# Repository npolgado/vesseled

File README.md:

# vesseled
addressable led code and hardware source. using addressable LEDS and creating a custom board to control and productize

Hardware:
- [x] Base prototyped idea
- [ ] Create a custom board to control addressable LEDS

Software:
- [x] Basic LED control
- [ ] track mouse poisition
- [ ] more input based lighting

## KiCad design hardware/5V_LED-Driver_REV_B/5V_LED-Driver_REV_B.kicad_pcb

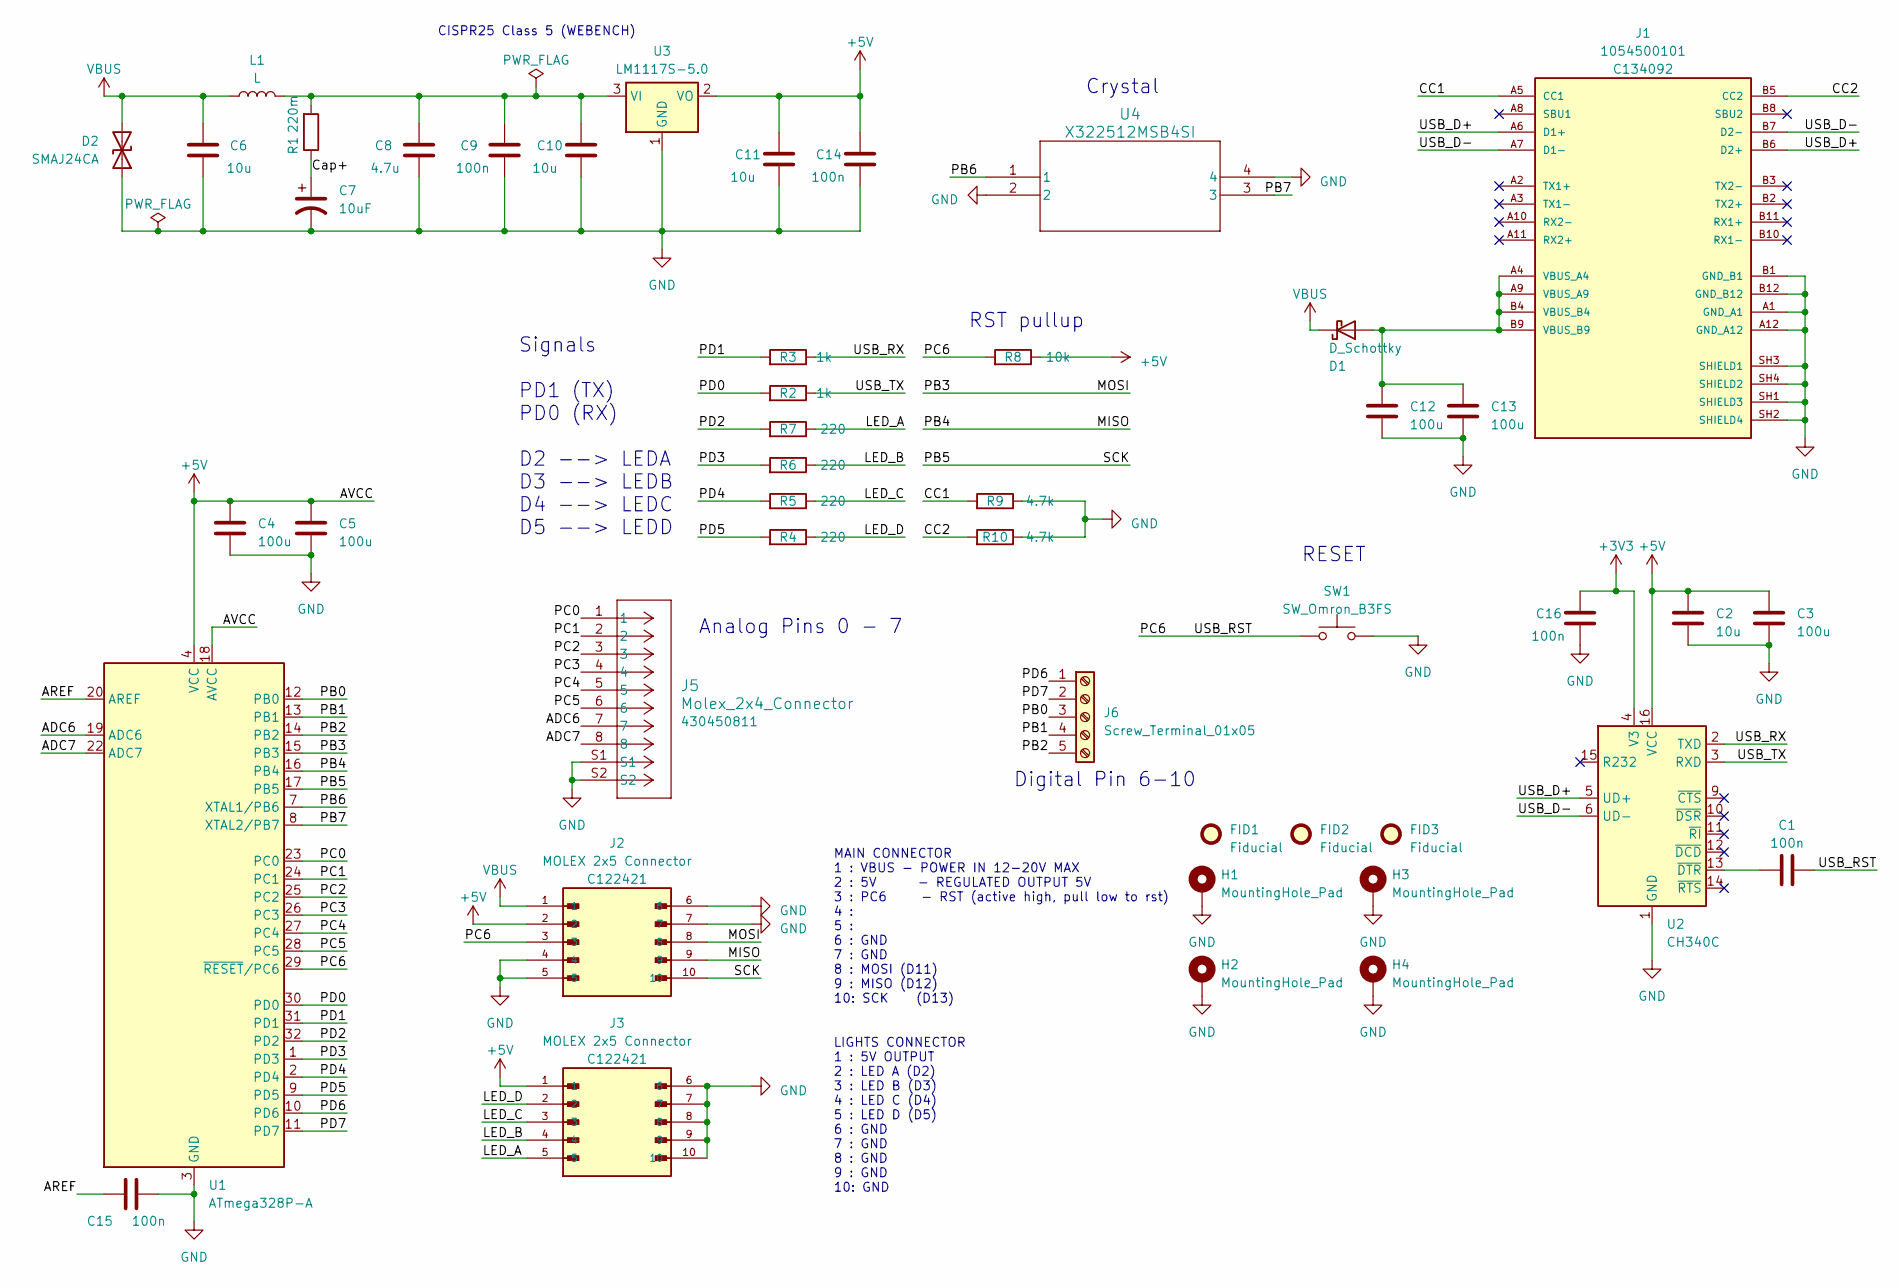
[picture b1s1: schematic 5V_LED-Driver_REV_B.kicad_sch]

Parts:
C1: 100n; C_0603_1608Metric
C2: 10u; C_0603_1608Metric
C3, C4, C5, C12, C13: 100u; C_0603_1608Metric
C6: 10u; L_1210_3225Metric; Manufacturer Part Number GRM32ER71H106KA12L; JLCPCB Part # C77102
C7: 10uF; CP_Elec_6.3x5.9; Manufacturer Part Number 50SVPF10M; JLCPCB Part # C2162323
C8: 4.7u; C_1206_3216Metric; Manufacturer Part Number GRM31CR71H475KA12L; JLCPCB Part # C77096
C9, C14, C15, C16: 100n; C_0603_1608Metric; Manufacturer Part Number GRM188R71H104KA93D; JLCPCB Part # C77055
C10, C11: 10u; C_0603_1608Metric; Manufacturer Part Number GRM188R71H104KA93D; JLCPCB Part # C77055
D1: D_Schottky; D_SMA
D2: SMAJ24CA; D_SMA; Manufacturer Part Number SMAJ24CA; JLCPCB Part # C148223
FID1, FID2, FID3: Fiducial; Fiducial_1mm_Mask2mm
H1, H2, H3, H4: MountingHole_Pad; MountingHole_3.2mm_M3_DIN965_Pad
J1: 1054500101; MOLEX_1054500101; PARTREV A7; JLCPCB Part # C134092
J2, J3: MOLEX 2x5 Connector; MOLEX_430451000; PARTREV G; JLCPCB Part # C122421
J5: Molex_2x4_Connector; MFG PN 430450811
J6: Screw_Terminal_01x05; TerminalBlock_bornier-5_P5.08mm
L1: L; L_0805_2012Metric; Manufacturer Part Number IHLP1212BZERR22M11; JLCPCB Part # C499512
R1: 220m; R_0603_1608Metric; Manufacturer Part Number RL0603FR-070R22L; JLCPCB Part # C326952
R2, R3: 1k; R_0603_1608Metric
R4, R5, R6, R7: 220; R_0603_1608Metric
R8: 10k; R_0603_1608Metric
R9, R10: 4.7k; R_0603_1608Metric
SW1: SW_Omron_B3FS; SW_SPST_Omron_B3FS-100xP
U1: ATmega328P-A; TQFP-32_7x7mm_P0.8mm
U2: CH340C; SOIC-16_3.9x9.9mm_P1.27mm
U3: LM1117S-5.0; TO-263-3_TabPin2
U4: X322512MSB4SI; SMD_2MSB4SI_YXC

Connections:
+3V3: C16.1, U2.4 (V3)
+5V: C2.1, C3.1, C4.1, C5.1, C11.1, C14.1, J2.2, J3.1, R8.1, U1.4 (VCC), U1.6 (VCC), U1.18 (AVCC), U2.16 (VCC), U3.2 (VO)
/ADC6: J5.7, U1.19 (ADC6)
/ADC7: J5.8, U1.22 (ADC7)
/AREF: C15.1, U1.20 (AREF)
/CC1: J1.A5 (CC1), R9.2
/CC2: J1.B5 (CC2), R10.2
/Cap+: C7.1, R1.1
/LED_A: J3.5, R7.1
/LED_B: J3.4, R6.1
/LED_C: J3.3, R5.1
/LED_D: J3.2, R4.1
/MISO: J2.9, U1.16 (PB4)
/MOSI: J2.8, U1.15 (PB3)
/PB0: J6.3, U1.12 (PB0)
/PB1: J6.4, U1.13 (PB1)
/PB2: J6.5, U1.14 (PB2)
/PB5: J2.10, U1.17 (PB5)
/PB6: U1.7 (XTAL1/PB6), U4.1
/PB7: U1.8 (XTAL2/PB7), U4.3
/PC0: J5.1, U1.23 (PC0)
/PC1: J5.2, U1.24 (PC1)
/PC2: J5.3, U1.25 (PC2)
/PC3: J5.4, U1.26 (PC3)
/PC4: J5.5, U1.27 (PC4)
/PC5: J5.6, U1.28 (PC5)
/PC6: C1.1, J2.3, R8.2, SW1.1, U1.29 (~RESET/PC6)
/PD0: R2.2, U1.30 (PD0)
/PD1: R3.2, U1.31 (PD1)
/PD2: R7.2, U1.32 (PD2)
/PD3: R6.2, U1.1 (PD3)
/PD4: R5.2, U1.2 (PD4)
/PD5: R4.2, U1.9 (PD5)
/PD6: J6.1, U1.10 (PD6)
/PD7: J6.2, U1.11 (PD7)
/USB_D+: J1.A6 (D1+), J1.B6 (D2+), U2.5 (UD+)
/USB_D-: J1.A7 (D1-), J1.B7 (D2-), U2.6 (UD-)
/USB_RX: R3.1, U2.2 (TXD)
/USB_TX: R2.1, U2.3 (RXD)
GND: C2.2, C3.2, C4.2, C5.2, C6.2, C7.2, C8.2, C9.2, C10.2, C11.2, C12.2, C13.2, C14.2, C15.2, C16.2, D2.1 (A1), H1.1, H2.1, H3.1, H4.1, J1.A1 (GND_A1), J1.A12 (GND_A12), J1.B1 (GND_B1), J1.B12 (GND_B12), J1.SH1 (SHIELD3), J1.SH2 (SHIELD4), J1.SH3 (SHIELD1), J1.SH4 (SHIELD2), J2.4, J2.5, J2.6, J2.7, J3.6, J3.7, J3.8, J3.9, J3.10, J5.S1, J5.S2, R9.1, R10.1, SW1.2, U1.3 (GND), U1.5 (GND), U1.21 (GND), U2.1 (GND), U3.1 (GND), U4.2, U4.4
unnamed: C8.1, C9.1, C10.1, L1.2, R1.2, U3.3 (VI)
unnamed: C12.1, C13.1, D1.2 (A), J1.A4 (VBUS_A4), J1.A9 (VBUS_A9), J1.B4 (VBUS_B4), J1.B9 (VBUS_B9)
unnamed: C1.2, U2.13 (~DTR)
VBUS: C6.1, D1.1 (K), D2.2 (A2), J2.1, L1.1

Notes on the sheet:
Crystal
RST pullup
CISPR25 Class 5 (WEBENCH)
Digital Pin 6-10
MAIN CONNECTOR 1 : VBUS - POWER IN 12-20V MAX 2 : 5V - REGULATED OUTPUT 5V 3 : PC6 - RST (active high, pull low to rst) 4 : 5 : 6 : GND 7 : GND 8 : MOSI (D11) 9 : MISO (D12) 10: SCK (D13)
Analog Pins 0 - 7
RESET
Signals PD1 (TX) PD0 (RX) D2 --> LEDA D3 --> LEDB D4 --> LEDC D5 --> LEDD
LIGHTS CONNECTOR 1 : 5V OUTPUT 2 : LED A (D2) 3 : LED B (D3) 4 : LED C (D4) 5 : LED D (D5) 6 : GND 7 : GND 8 : GND 9 : GND 10: GND

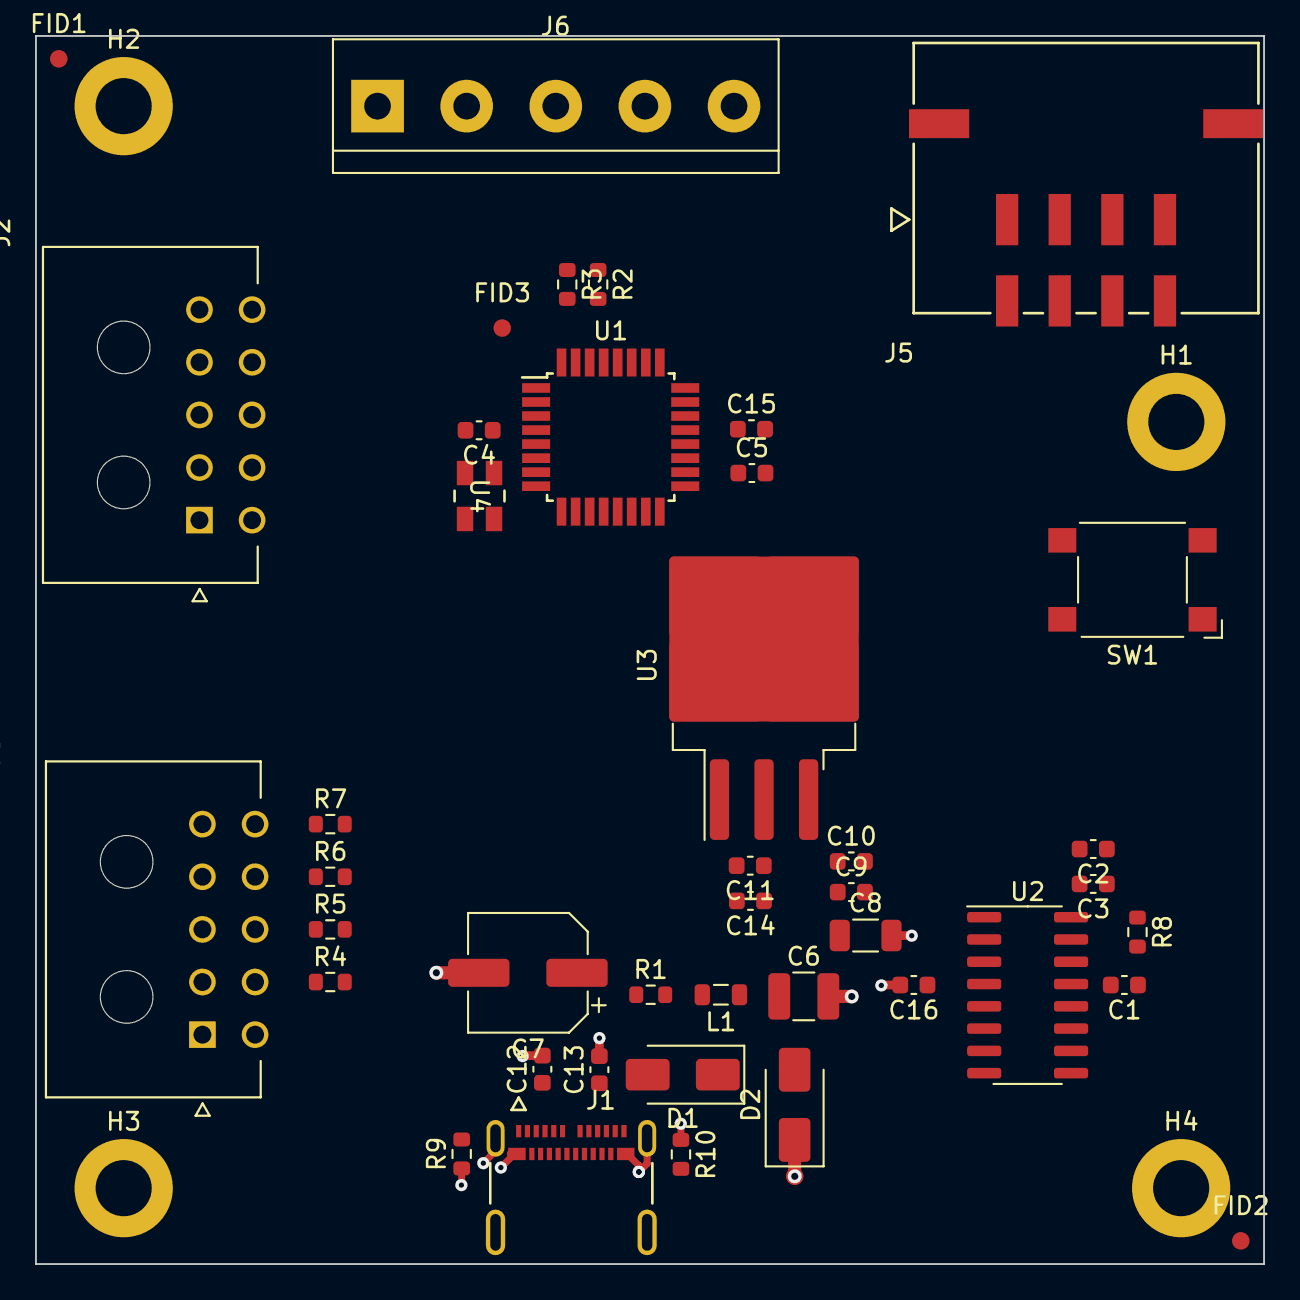
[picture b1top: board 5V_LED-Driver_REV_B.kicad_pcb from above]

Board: 4 copper layers, 70.0 x 70.0 mm, 46 parts (0 on the bottom side), 44 nets.

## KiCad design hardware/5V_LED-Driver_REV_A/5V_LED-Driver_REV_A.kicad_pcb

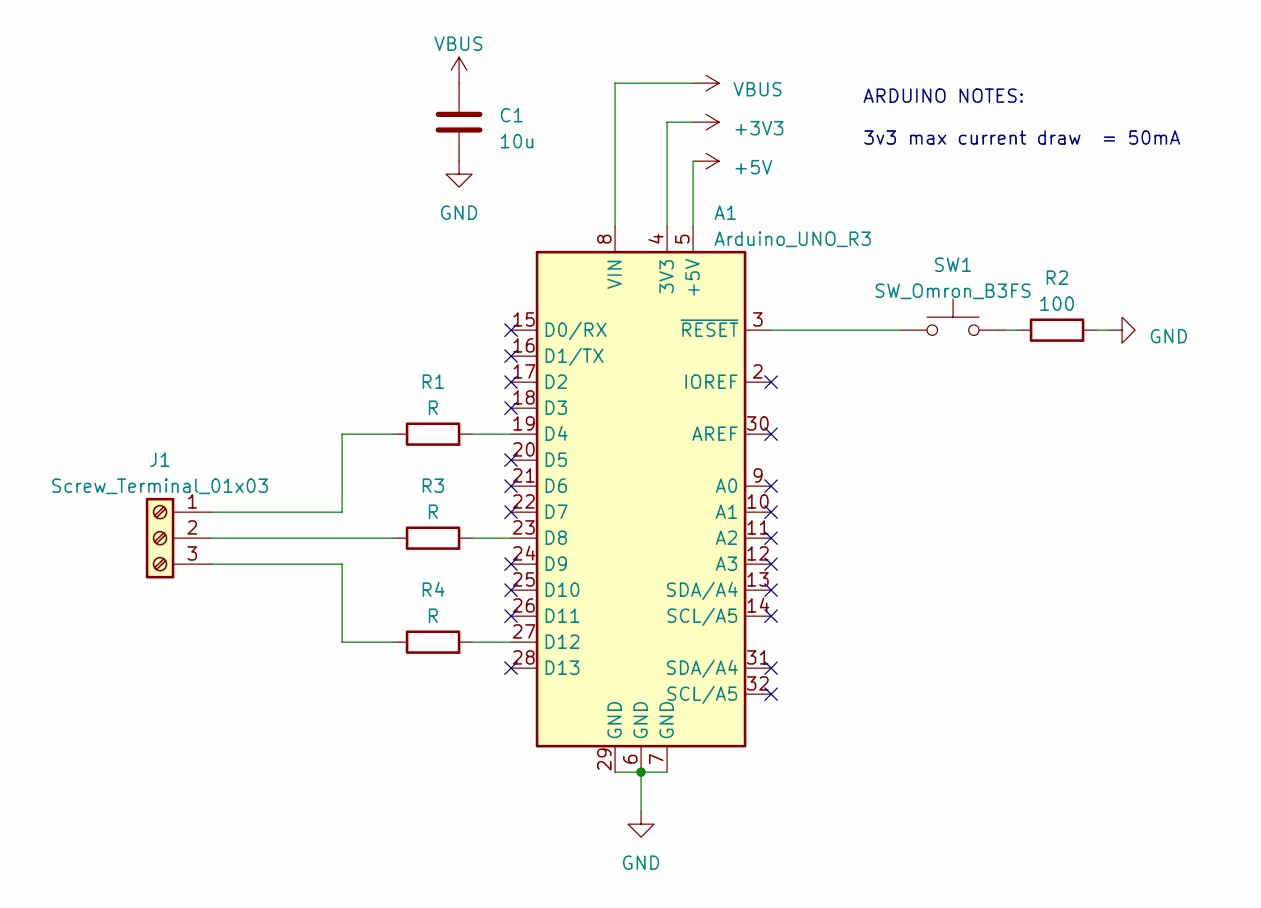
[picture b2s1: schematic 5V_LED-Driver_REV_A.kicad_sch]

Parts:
A1: Arduino_UNO_R3
C1: 10u; C_0603_1608Metric
J1: Screw_Terminal_01x03; TerminalBlock_Phoenix_MKDS-3-3-5.08_1x03_P5.08mm_Horizontal
R1, R3, R4: R; R_0603_1608Metric
R2: 100; R_0603_1608Metric
SW1: SW_Omron_B3FS; SW_SPST_Omron_B3FS-100xP

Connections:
+3V3: A1.4 (3V3)
+5V: A1.5 (+5V)
GND: A1.6 (GND), A1.7 (GND), A1.29 (GND), C1.2, R2.2
unnamed: A1.19 (D4), R1.2
unnamed: A1.23 (D8), R3.2
unnamed: A1.27 (D12), R4.2
unnamed: A1.3 (~RESET), SW1.1
unnamed: J1.1, R1.1
unnamed: J1.2, R3.1
unnamed: J1.3, R4.1
unnamed: R2.1, SW1.2
VBUS: A1.8 (VIN), C1.1

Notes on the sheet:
ARDUINO NOTES: 3v3 max current draw = 50mA

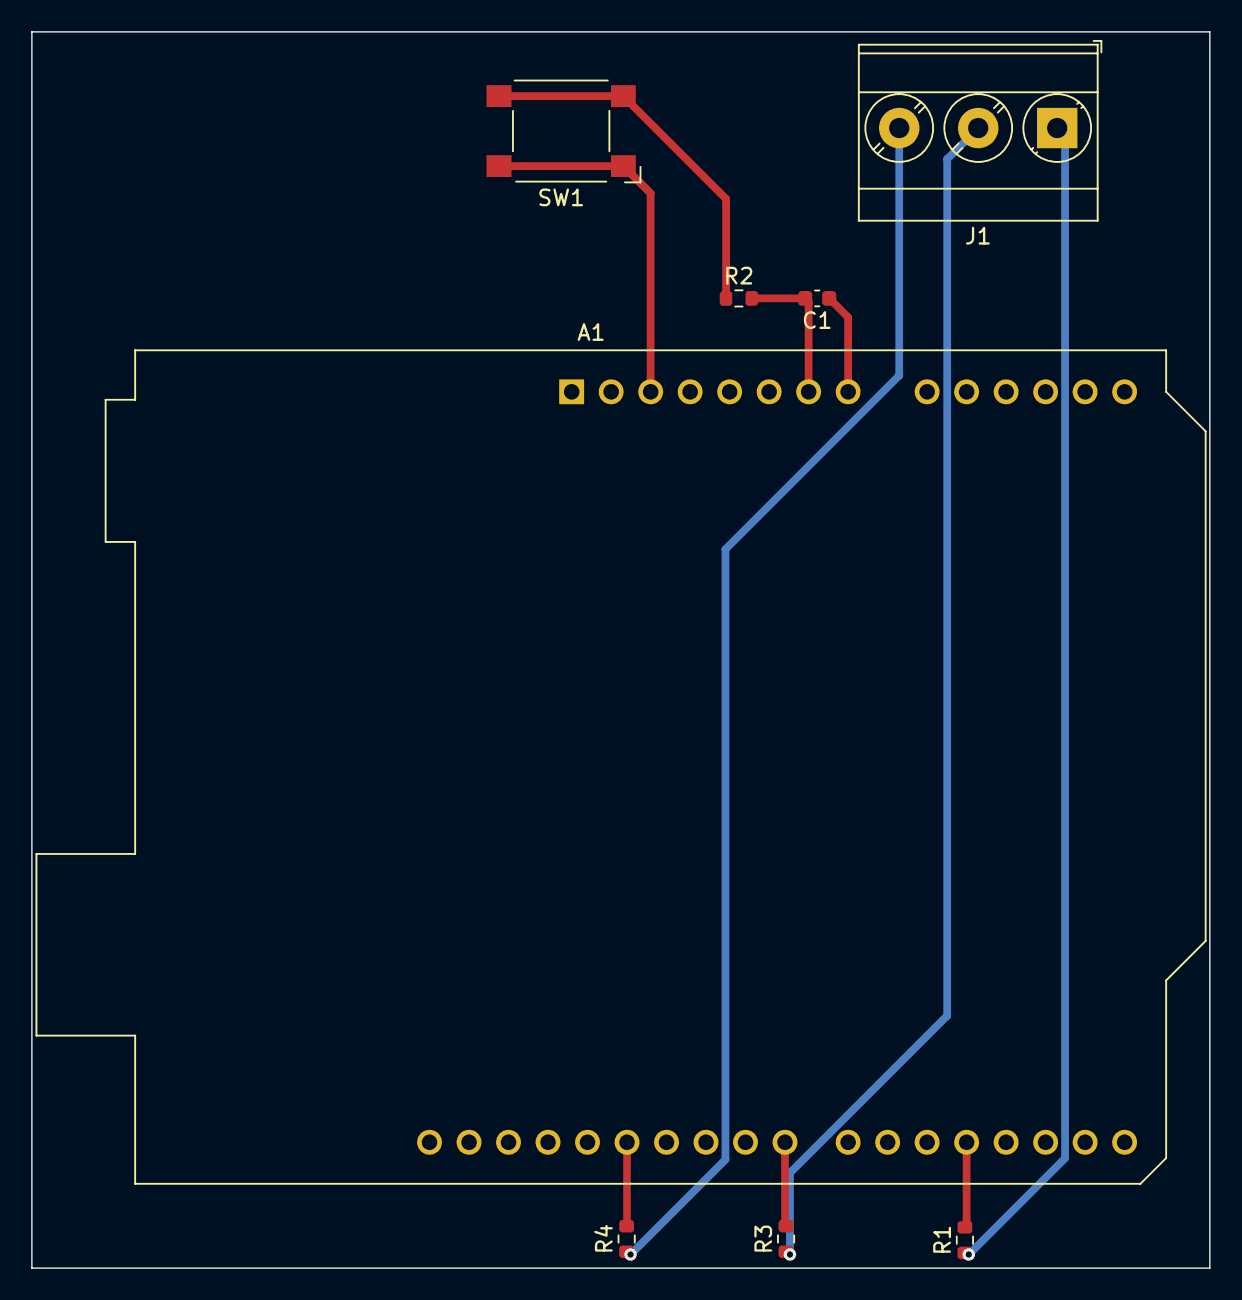
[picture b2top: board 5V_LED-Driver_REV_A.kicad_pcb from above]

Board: 2 copper layers, 75.7 x 79.5 mm, 8 parts (0 on the bottom side), 10 nets.

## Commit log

2024-03-10 init commit with current work
2024-03-12 dual_strip action
2024-03-14 demo randomly on both strips
2024-03-14 mouse tracker basic working :)
2024-04-29 pc haptics
